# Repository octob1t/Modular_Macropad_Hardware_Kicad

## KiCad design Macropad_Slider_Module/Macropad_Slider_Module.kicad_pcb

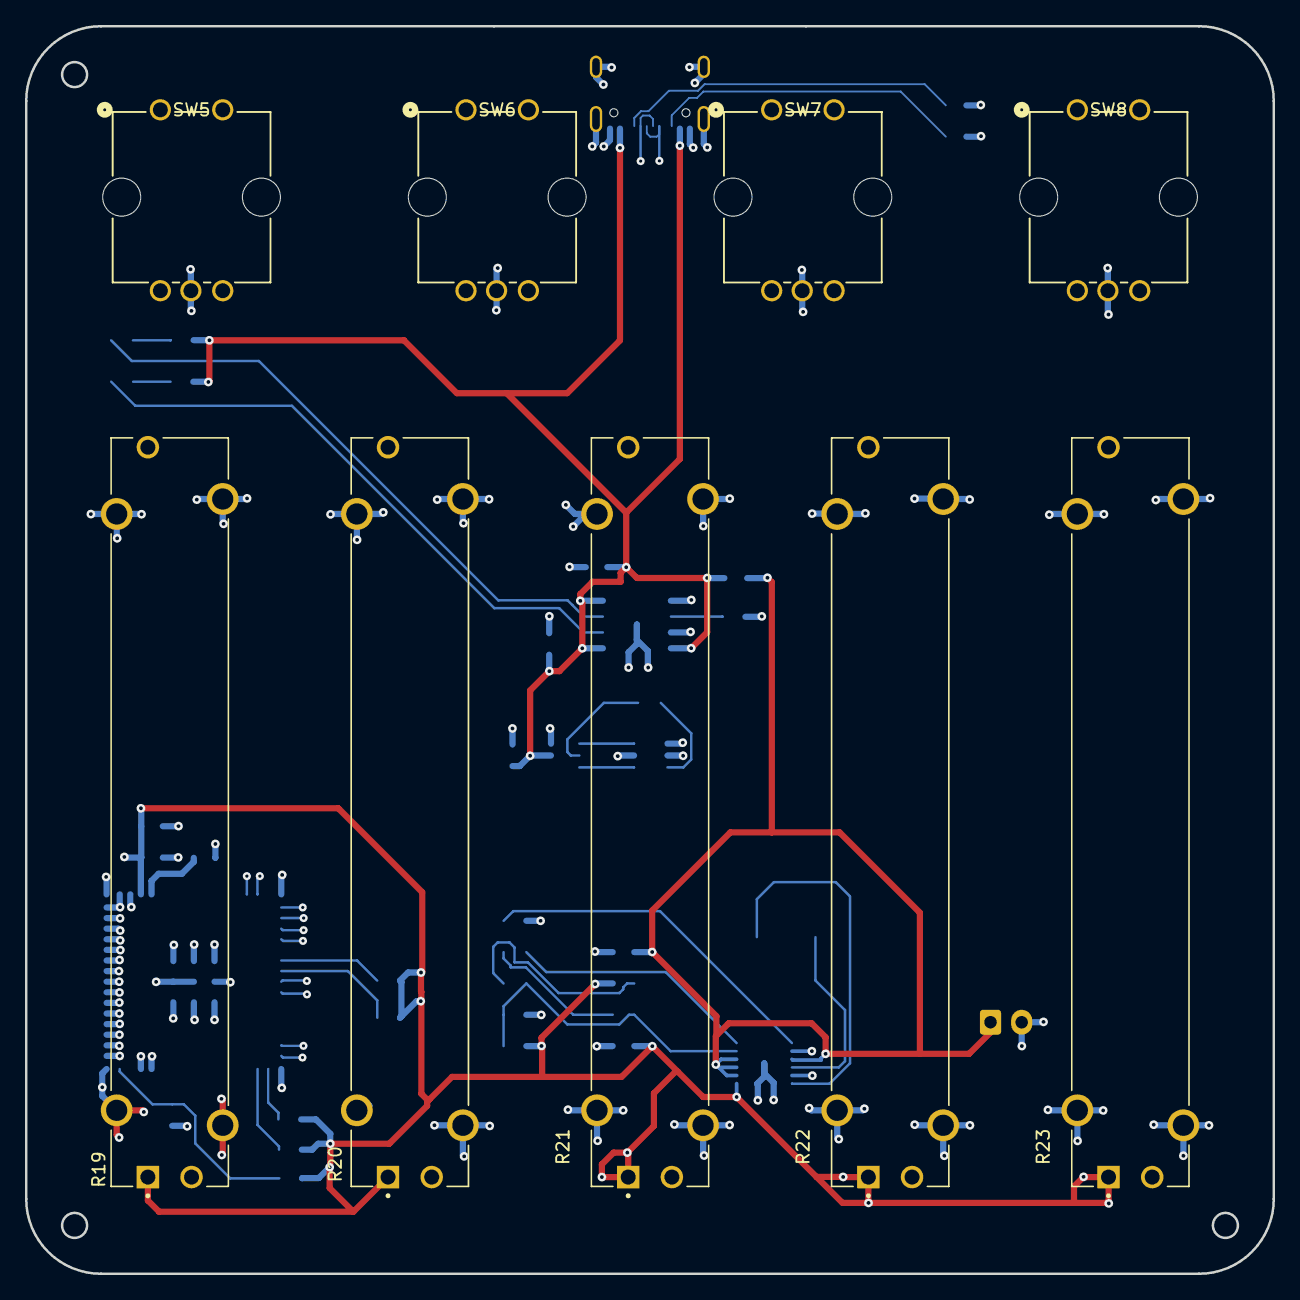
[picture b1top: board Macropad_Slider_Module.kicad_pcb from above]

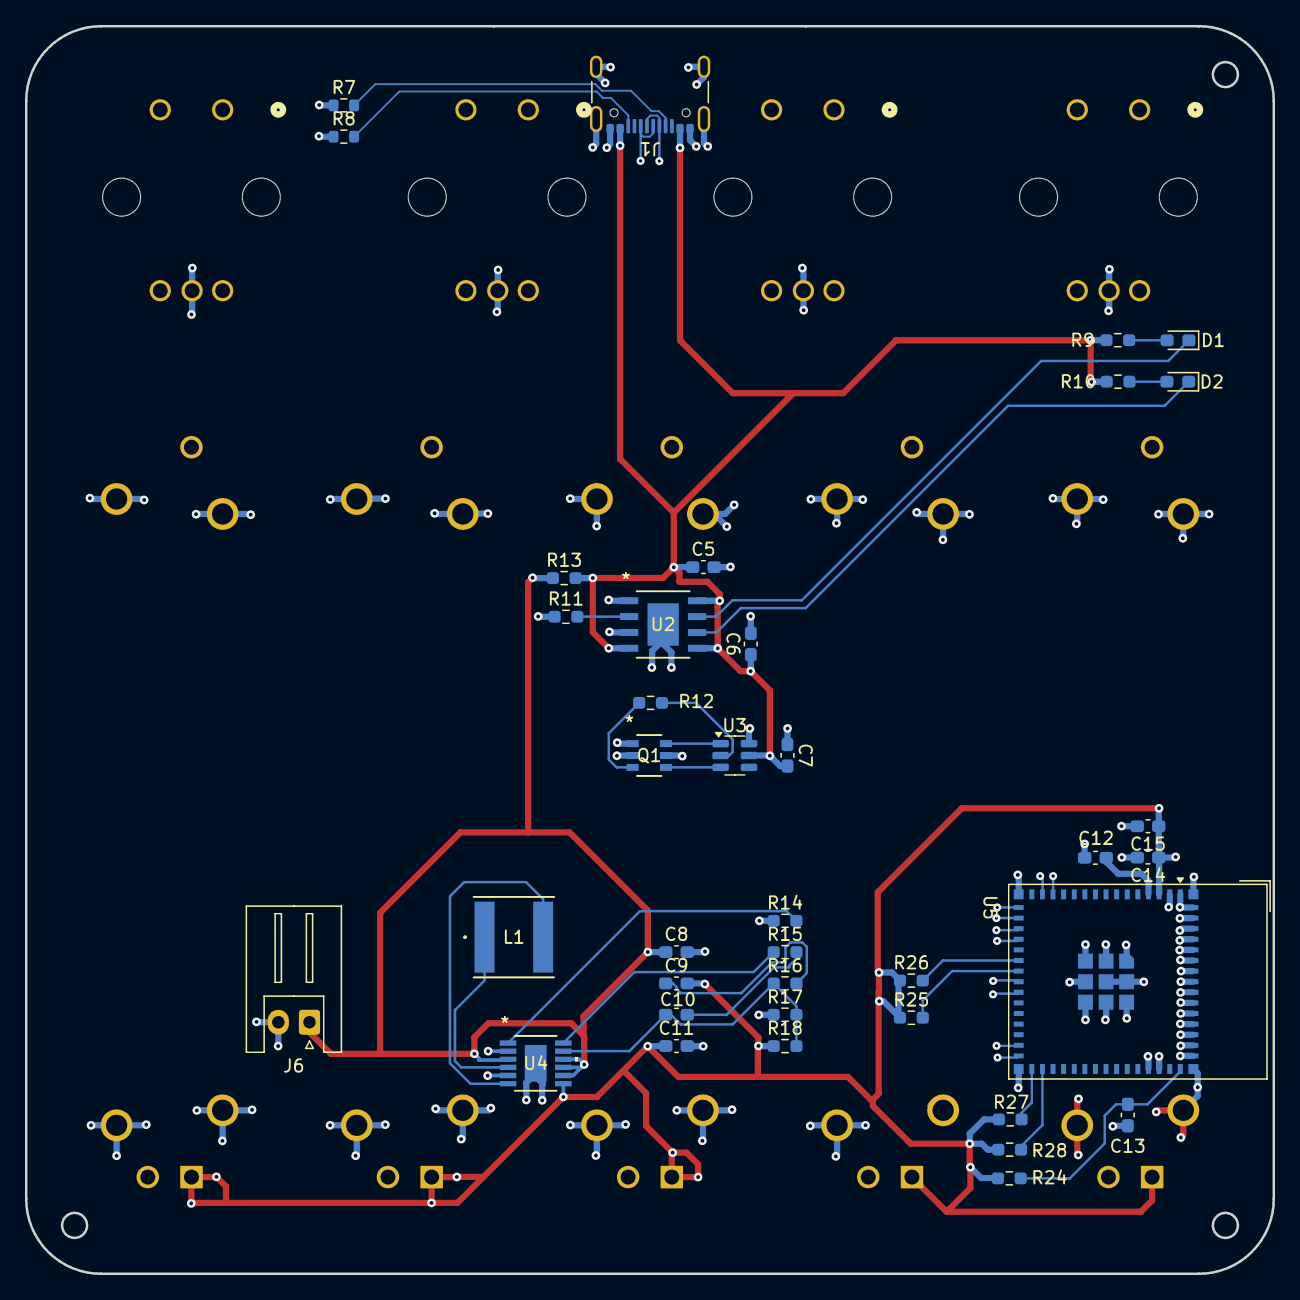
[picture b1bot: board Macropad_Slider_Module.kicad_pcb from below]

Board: 4 copper layers, 100.0 x 100.0 mm, 47 parts (38 on the bottom side), 38 nets.

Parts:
C5, C6, C8, C15: 10uF; C_0603_1608Metric_Pad1.08x0.95mm_HandSolder
C7, C12, C13, C14: .1uF; C_0603_1608Metric_Pad1.08x0.95mm_HandSolder
C9: 47uF; C_0603_1608Metric_Pad1.08x0.95mm_HandSolder
C10: 220pF; C_0603_1608Metric_Pad1.08x0.95mm_HandSolder
C11: 22pF; C_0603_1608Metric_Pad1.08x0.95mm_HandSolder
D1, D2: LED_Small; LED_0603_1608Metric_Pad1.05x0.95mm_HandSolder
J1: USB_C_Receptacle_USB2.0_16P; USB_C_Receptacle_GCT_USB4105-xx-A_16P_TopMnt_Horizontal
J6: Conn_01x02_Socket; JST_XH_S2B-XH-A_1x02_P2.50mm_Horizontal
L1: 4.7uH; IND_TAIYO_NR6028_TAY
Q1: FS8205A; SOT-23-6L_TCP
R7, R8: 5k1; R_0603_1608Metric
R9, R10: 1K; R_0603_1608Metric_Pad0.98x0.95mm_HandSolder
R11: 1K3; R_0603_1608Metric_Pad0.98x0.95mm_HandSolder
R12: 100k; R_0603_1608Metric_Pad0.98x0.95mm_HandSolder
R13: 100; R_0603_1608Metric_Pad0.98x0.95mm_HandSolder
R14: 332k; R_0603_1608Metric_Pad0.98x0.95mm_HandSolder
R15: 49K9; R_0603_1608Metric_Pad0.98x0.95mm_HandSolder
R16: 6K49; R_0603_1608Metric_Pad0.98x0.95mm_HandSolder
R17: 221K; R_0603_1608Metric_Pad0.98x0.95mm_HandSolder
R18: 1000k; R_0603_1608Metric_Pad0.98x0.95mm_HandSolder
R19, R20, R21, R22, R23: PTA4543-2015CPB102; TRIM_PTA4543-2015CPB102
R24: 10K; R_0603_1608Metric_Pad0.98x0.95mm_HandSolder
R25, R26, R27, R28: 10k; R_0603_1608Metric_Pad0.98x0.95mm_HandSolder
SW5, SW6, SW7, SW8: RotaryEncoder; PEC12R-4x15F-Sxxxx_BRN
U2: TP4056; ESOP8_TPW
U3: DW01A; SOT-23-6
U4: LTC3536EMSE-PBF; MSOP-12_MSE_LIT
U5: ESP32-S3-MINI-1; ESP32-S2-MINI-1

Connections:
+3V3: C9.2, C11.1, C14.1, C15.1, R18.1, R19.1, R20.1, R21.1, R22.1, R23.1, R24.1, R25.1, R26.1, R27.1, R28.1, U4.7 (VOUT), U5.3 (3V3)
/BOOT: C12.1, U5.4 (IO0)
/ESP32_EN: C13.1, R24.2, U5.45 (EN)
BAT+: C8.1, J6.1, R13.1, U4.3 (MODE/SYNC), U4.8 (VIN), U4.9 (VIN), U4.10 (*SHDN)
GND: C5.2, C6.2, C7.1, C8.2, C11.2, C12.2, C13.2, C14.2, C15.2, J1.A1 (GND), J1.A12 (GND), J1.B1 (GND), J1.B12 (GND), J1.S1 (SHIELD), J6.2, Q1.1 (S1), Q1.2 (D12), Q1.5 (D12), R7.1, R8.1, R11.1, R14.1, R17.1, R19.SH1 (SHIELD), R19.SH2 (SHIELD__1), R19.SH3 (SHIELD__2), R19.SH4 (SHIELD__3), R20.SH1 (SHIELD), R20.SH2 (SHIELD__1), R20.SH3 (SHIELD__2), R20.SH4 (SHIELD__3), R21.SH1 (SHIELD), R21.SH2 (SHIELD__1), R21.SH3 (SHIELD__2), R21.SH4 (SHIELD__3), R22.SH1 (SHIELD), R22.SH2 (SHIELD__1), R22.SH3 (SHIELD__2), R22.SH4 (SHIELD__3), R23.SH1 (SHIELD), R23.SH2 (SHIELD__1), R23.SH3 (SHIELD__2), R23.SH4 (SHIELD__3), SW5.C, SW6.C, SW7.C, SW8.C, U2.1 (TEMP), U2.3 (GND), U2.9 (GND), U3.6 (GND), U4.2 (SGND), U4.5 (PGND), U4.13 (EPAD), U5.1 (GND), U5.2 (GND), U5.42 (GND), U5.43 (GND), U5.46 (GND), U5.47 (GND), U5.48 (GND), U5.49 (GND), U5.50 (GND), U5.51 (GND), U5.52 (GND), U5.53 (GND), U5.54 (GND), U5.55 (GND), U5.56 (GND), U5.57 (GND), U5.58 (GND), U5.59 (GND), U5.60 (GND), U5.61 (GND), U5.62 (GND), U5.63 (GND), U5.64 (GND), U5.65 (GND)
unnamed: C9.1, R16.2
unnamed: C10.1, R15.2
unnamed: D1.2 (A), R9.2
unnamed: D1.1 (K), U2.7 (*CHRG)
unnamed: D2.2 (A), R10.2
unnamed: D2.1 (K), U2.6 (*STDBY)
unnamed: J1.A5 (CC1), R7.2
unnamed: J1.B5 (CC2), R8.2
unnamed: Q1.6 (G1), U3.1 (OD)
unnamed: Q1.4 (G2), U3.3 (OC)
unnamed: Q1.3 (S2), R12.2
unnamed: R11.2, U2.2 (PROG)
unnamed: R12.1, U3.2 (CS)
unnamed: C10.2, R16.1, R17.2, R18.2, U4.11 (FB)
unnamed: R14.2, U4.1 (RT)
unnamed: L1.1, U4.4 (SW1)
unnamed: L1.2, U4.6 (SW2)
unnamed: R15.1, U4.12 (VC)
unnamed: R26.2, U5.21 (IO17)
unnamed: R25.2, U5.22 (IO18)
unnamed: R27.2, U5.31 (IO35)
unnamed: R28.2, U5.32 (IO36)
R1A: SW5.A, U5.13 (IO9)
R1B: SW5.B, U5.14 (IO10)
R2A: SW6.A, U5.16 (IO12)
R2B: SW6.B, U5.17 (IO13)
R3A: SW7.A, U5.18 (IO14)
R3B: SW7.B, U5.19 (IO15)
R4A: SW8.A, U5.29 (IO34)
R4B: SW8.B, U5.30 (IO48)
USB_N: J1.A7 (D-), J1.B7 (D-), U5.23 (IO19)
USB_P: J1.A6 (D+), J1.B6 (D+), U5.24 (IO20)
VBUS: C5.1, C6.1, C7.2, J1.A4 (VBUS), J1.A9 (VBUS), J1.B4 (VBUS), J1.B9 (VBUS), R9.1, R10.1, R13.2, U2.4 (VCC), U2.5 (BAT), U2.8 (CE), U3.5 (VCC)

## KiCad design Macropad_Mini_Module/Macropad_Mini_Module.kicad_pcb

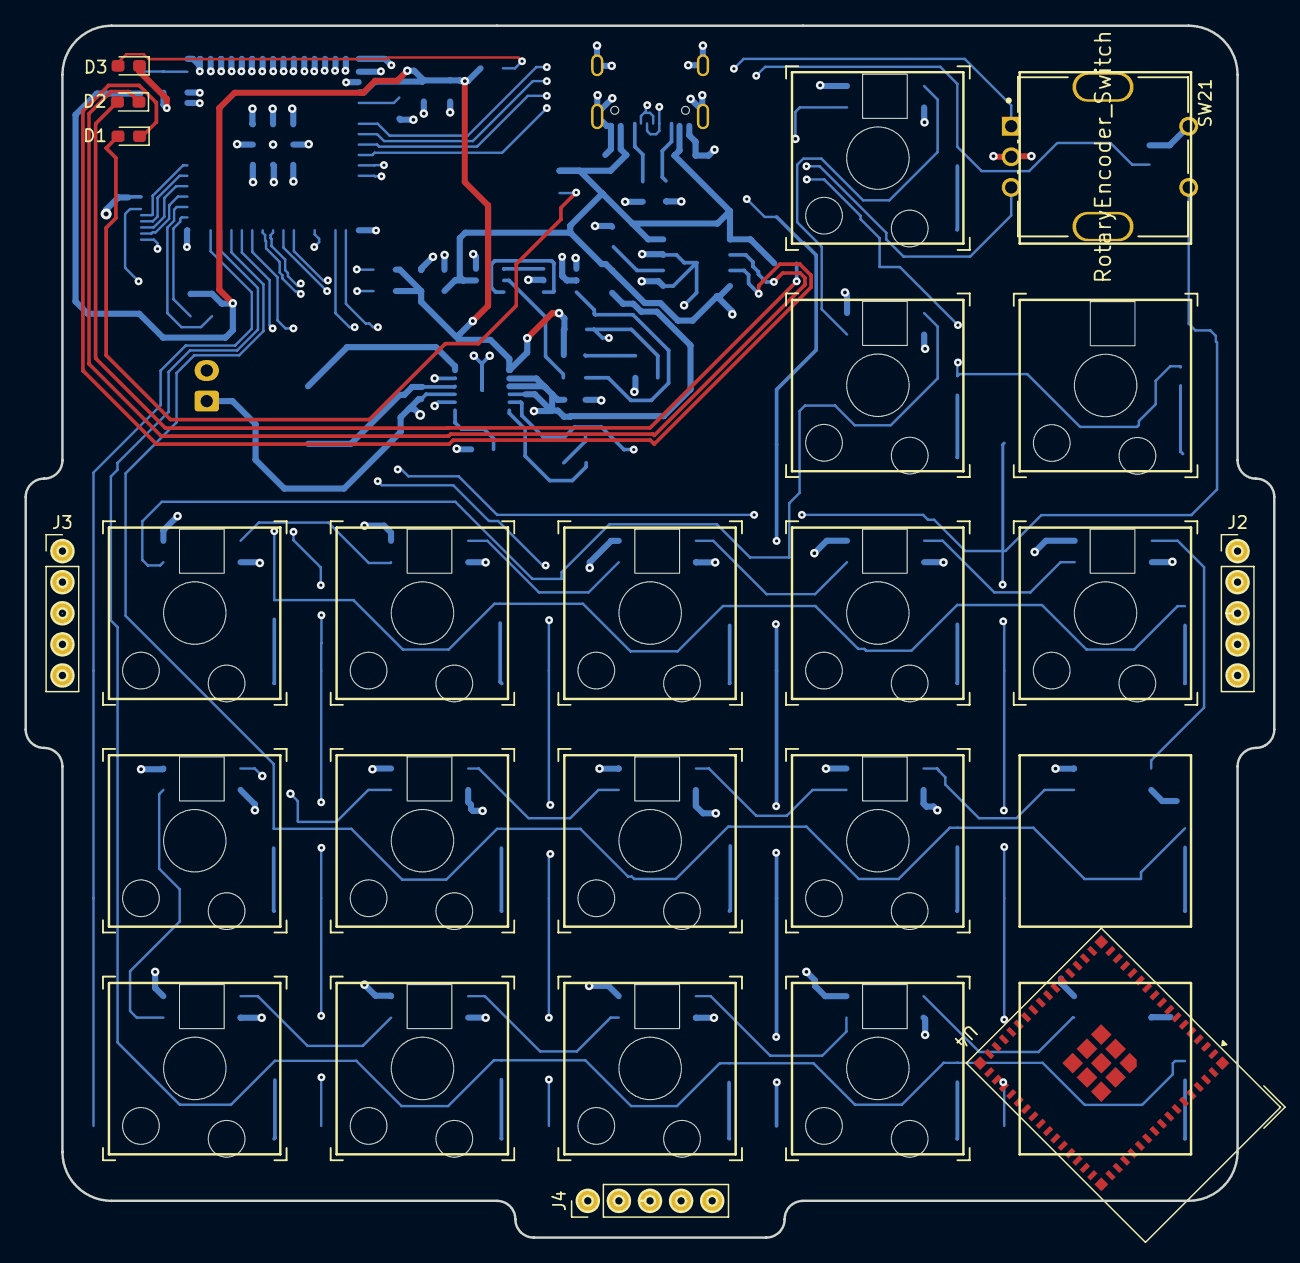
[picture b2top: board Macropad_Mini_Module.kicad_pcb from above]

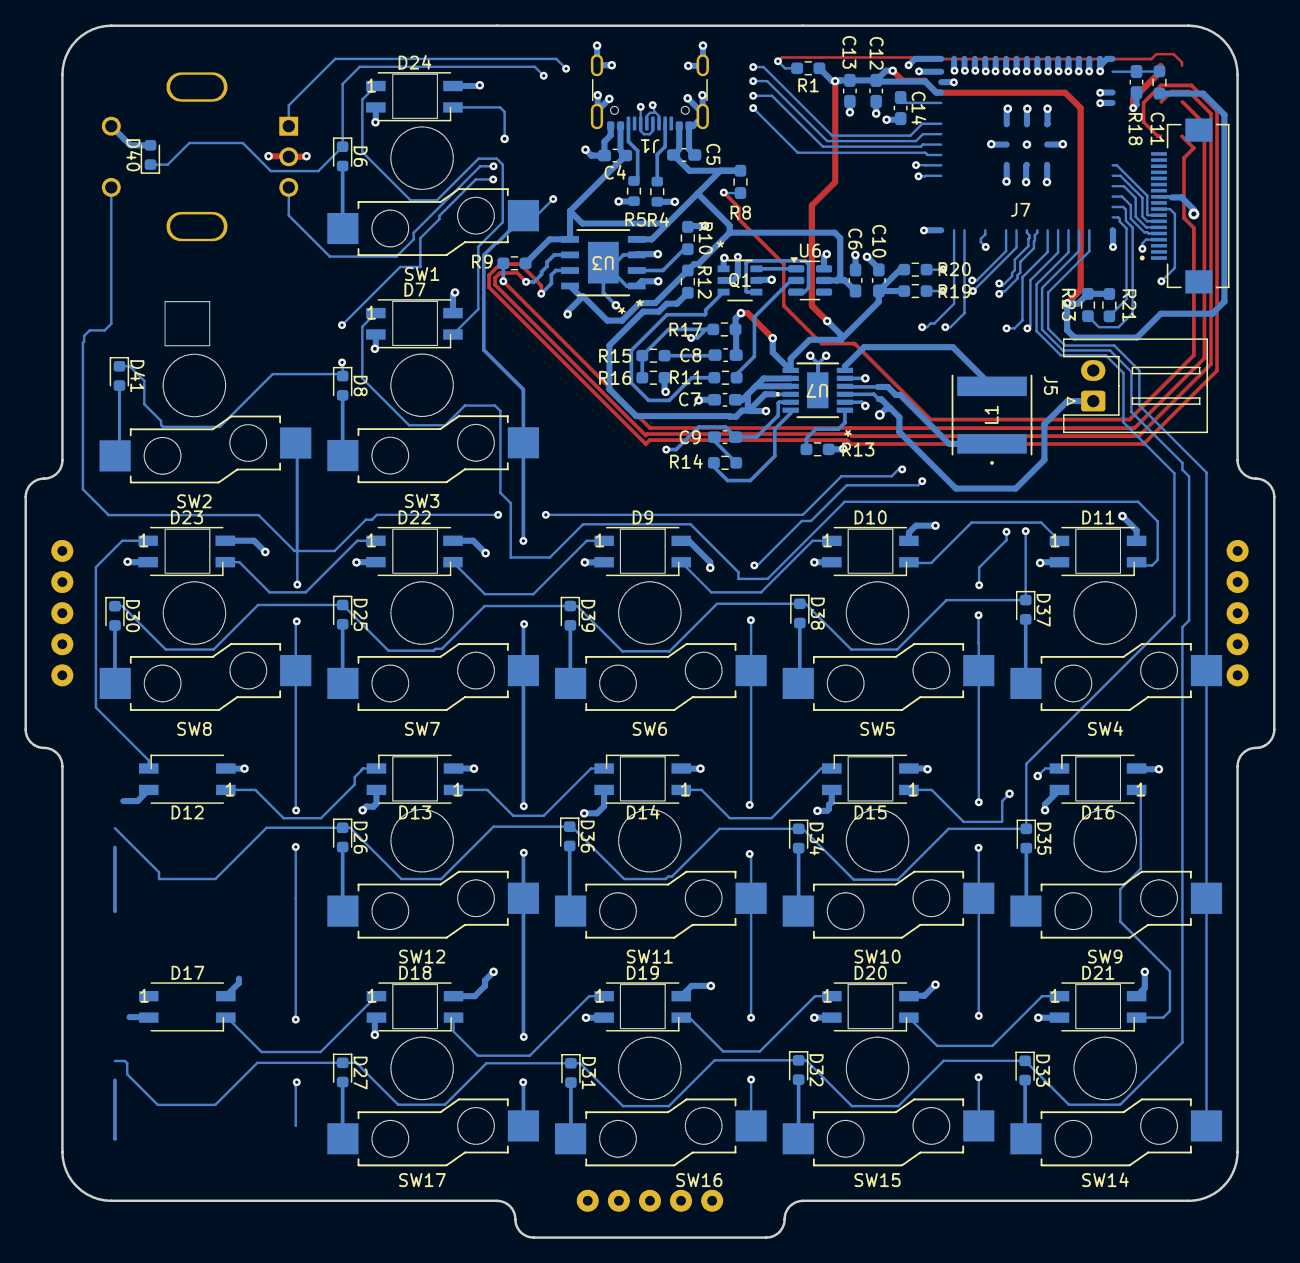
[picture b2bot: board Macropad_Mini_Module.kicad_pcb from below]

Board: 4 copper layers, 102.0 x 99.0 mm, 95 parts (71 on the bottom side), 82 nets.

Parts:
C4, C5, C7, C13: 10uF; C_0603_1608Metric_Pad1.08x0.95mm_HandSolder
C6, C11, C12, C14: .1uF; C_0603_1608Metric_Pad1.08x0.95mm_HandSolder
C8: 47uF; C_0603_1608Metric_Pad1.08x0.95mm_HandSolder
C9: 220pF; C_0603_1608Metric_Pad1.08x0.95mm_HandSolder
C10: 22pF; C_0603_1608Metric_Pad1.08x0.95mm_HandSolder
D1, D2, D3: LED_Small; LED_0603_1608Metric_Pad1.05x0.95mm_HandSolder
D6, D8, D25, D26, D27, D30, D31, D32, D33, D34, D35, D36, D37, D38, D39, D40, D41: D; D_0603_1608Metric
D7, D9, D10, D11, D12, D13, D14, D15, D16, D17, D18, D19, D20, D21, D22, D23, D24: SK6812MINI; LED_SK6812MINI_PLCC4_3.5x3.5mm_P1.75mm_1_Hole_Pads
J1: USB_C_Receptacle_USB2.0_16P; USB_C_Receptacle_GCT_USB4105-xx-A_16P_TopMnt_Horizontal
J2, J3, J4: Conn_01x05_Socket; PinHeader_1x05_P2.54mm_Vertical_Adafruit
J5: Conn_01x02_Socket; JST_XH_S2B-XH-A_1x02_P2.50mm_Horizontal
J7: TF31-18S-0.5SH_800_; HRS_TF31-18S-0.5SH_800_
L1: 4.7uH; IND_TAIYO_NR6028_TAY
Q1: FS8205A; SOT-23-6L_TCP
R1, R8, R9: 1K; R_0603_1608Metric_Pad0.98x0.95mm_HandSolder
R4, R5: 5k1; R_0603_1608Metric
R10: 1K3; R_0603_1608Metric_Pad0.98x0.95mm_HandSolder
R11: 100k; R_0603_1608Metric_Pad0.98x0.95mm_HandSolder
R12: 100; R_0603_1608Metric_Pad0.98x0.95mm_HandSolder
R13: 332k; R_0603_1608Metric_Pad0.98x0.95mm_HandSolder
R14: 49K9; R_0603_1608Metric_Pad0.98x0.95mm_HandSolder
R15: 6K49; R_0603_1608Metric_Pad0.98x0.95mm_HandSolder
R16: 221K; R_0603_1608Metric_Pad0.98x0.95mm_HandSolder
R17: 1000k; R_0603_1608Metric_Pad0.98x0.95mm_HandSolder
R18: 10K; R_0603_1608Metric_Pad0.98x0.95mm_HandSolder
R19, R20, R21, R23: 10k; R_0603_1608Metric_Pad0.98x0.95mm_HandSolder
SW1, SW2, SW3, SW4, SW5, SW6, SW7, SW8, SW9, SW10, SW11, SW12, SW14, SW15, SW16, SW17: SW_MEC_5G; Gateron_Low_Profile_Socket_LED
SW21: RotaryEncoder_Switch; Bourns-PEC11R-4220F-S0024-0-0-0
U3: TP4056; ESOP8_TPW
U4: ESP32-S3-MINI-1; ESP32-S2-MINI-1
U6: DW01A; SOT-23-6
U7: LTC3536EMSE-PBF; MSOP-12_MSE_LIT

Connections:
+3V3: C8.2, C10.1, C12.1, C13.1, R1.1, R17.1, R18.1, R19.1, R20.1, R21.1, R23.1, U4.3 (3V3), U7.7 (VOUT)
/BOOT: C14.1, U4.4 (IO0)
/ESP32_EN: C11.1, R18.2, U4.45 (EN)
/MISO: J7.7, U4.35 (IO39)
/MOSI: J7.6, U4.34 (IO38)
/RST: J7.4, U4.19 (IO15)
/SCK: J7.8, U4.36 (IO40)
/TFTCS: J7.5, U4.33 (IO37)
BAT+: C7.1, J5.1, R12.1, U7.3 (MODE/SYNC), U7.8 (VIN), U7.9 (VIN), U7.10 (*SHDN)
Col0: SW4.1, SW9.1, SW14.1, U4.29 (IO34)
Col1: SW5.1, SW10.1, SW15.1, U4.25 (IO21)
Col2: SW6.1, SW11.1, SW16.1, U4.17 (IO13)
Col3: SW1.1, SW3.1, SW7.1, SW12.1, SW17.1, U4.10 (IO6)
Col4: SW2.1, SW8.1, SW21.S2, U4.16 (IO12)
GND: C4.2, C5.2, C6.1, C7.2, C10.2, C11.2, C12.2, C13.2, C14.2, D3.1 (K), D7.2 (VSS), D9.2 (VSS), D10.2 (VSS), D11.2 (VSS), D12.2 (VSS), D13.2 (VSS), D14.2 (VSS), D15.2 (VSS), D16.2 (VSS), D17.2 (VSS), D18.2 (VSS), D19.2 (VSS), D20.2 (VSS), D21.2 (VSS), D22.2 (VSS), D23.2 (VSS), D24.2 (VSS), J1.A1 (GND), J1.A12 (GND), J1.B1 (GND), J1.B12 (GND), J1.S1 (SHIELD), J5.2, J7.9, Q1.1 (S1), Q1.2 (D12), Q1.5 (D12), R4.1, R5.1, R10.1, R13.1, R16.1, SW21.C, U3.1 (TEMP), U3.3 (GND), U3.9 (GND), U4.1 (GND), U4.2 (GND), U4.42 (GND), U4.43 (GND), U4.46 (GND), U4.47 (GND), U4.48 (GND), U4.49 (GND), U4.50 (GND), U4.51 (GND), U4.52 (GND), U4.53 (GND), U4.54 (GND), U4.55 (GND), U4.56 (GND), U4.57 (GND), U4.58 (GND), U4.59 (GND), U4.60 (GND), U4.61 (GND), U4.62 (GND), U4.63 (GND), U4.64 (GND), U4.65 (GND), U6.6 (GND), U7.2 (SGND), U7.5 (PGND), U7.13 (EPAD)
LED_GPIO: D24.3 (DIN), U4.11 (IO7)
unnamed: C8.1, R15.2
unnamed: C9.1, R14.2
unnamed: D1.2 (A), R8.2
unnamed: D1.1 (K), U3.7 (*CHRG)
unnamed: D2.2 (A), R9.2
unnamed: D2.1 (K), U3.6 (*STDBY)
unnamed: D3.2 (A), R1.2
unnamed: D6.2 (A), SW1.2
unnamed: D8.2 (A), SW3.2
unnamed: D10.3 (DIN), D11.1 (DOUT)
unnamed: D9.3 (DIN), D10.1 (DOUT)
unnamed: D7.1 (DOUT), D11.3 (DIN)
unnamed: D12.3 (DIN), D23.1 (DOUT)
unnamed: D12.1 (DOUT), D13.3 (DIN)
unnamed: D13.1 (DOUT), D14.3 (DIN)
unnamed: D14.1 (DOUT), D15.3 (DIN)
unnamed: D15.1 (DOUT), D16.3 (DIN)
unnamed: D16.1 (DOUT), D21.3 (DIN)
unnamed: D17.3 (DIN), D18.1 (DOUT)
unnamed: D18.3 (DIN), D19.1 (DOUT)
unnamed: D19.3 (DIN), D20.1 (DOUT)
unnamed: D20.3 (DIN), D21.1 (DOUT)
unnamed: D9.1 (DOUT), D22.3 (DIN)
unnamed: D22.1 (DOUT), D23.3 (DIN)
unnamed: D7.3 (DIN), D24.1 (DOUT)
unnamed: D25.2 (A), SW7.2
unnamed: D26.2 (A), SW12.2
unnamed: D27.2 (A), SW17.2
unnamed: D30.2 (A), SW8.2
unnamed: D31.2 (A), SW16.2
unnamed: D32.2 (A), SW15.2
unnamed: D33.2 (A), SW14.2
unnamed: D34.2 (A), SW10.2
unnamed: D35.2 (A), SW9.2
unnamed: D36.2 (A), SW11.2
unnamed: D37.2 (A), SW4.2
unnamed: D38.2 (A), SW5.2
unnamed: D39.2 (A), SW6.2
unnamed: D40.2 (A), SW21.S1
unnamed: D41.2 (A), SW2.2
unnamed: J1.A5 (CC1), R4.2
unnamed: J1.B5 (CC2), R5.2
unnamed: Q1.6 (G1), U6.1 (OD)
unnamed: Q1.4 (G2), U6.3 (OC)
unnamed: Q1.3 (S2), R11.2
unnamed: R10.2, U3.2 (PROG)
unnamed: R20.2, U4.21 (IO17)
unnamed: R19.2, U4.22 (IO18)
unnamed: R21.2, U4.31 (IO35)
unnamed: R23.2, U4.32 (IO36)
unnamed: R11.1, U6.2 (CS)
unnamed: C9.2, R15.1, R16.2, R17.2, U7.11 (FB)
unnamed: R13.2, U7.1 (RT)
unnamed: L1.1, U7.4 (SW1)
unnamed: L1.2, U7.6 (SW2)
unnamed: R14.1, U7.12 (VC)
RotaryA: SW21.A, U4.6 (IO2)
RotaryB: SW21.B, U4.8 (IO4)
Row0: D6.1 (K), D40.1 (K), U4.7 (IO3)
Row1: D8.1 (K), D41.1 (K), U4.9 (IO5)
Row2: D25.1 (K), D30.1 (K), D37.1 (K), D38.1 (K), D39.1 (K), U4.26 (IO26)
Row3: D26.1 (K), D34.1 (K), D35.1 (K), D36.1 (K), U4.27 (IO47)
Row4: D27.1 (K), D31.1 (K), D32.1 (K), D33.1 (K), U4.28 (IO33)
USB_N: J1.A7 (D-), J1.B7 (D-), U4.23 (IO19)
USB_P: J1.A6 (D+), J1.B6 (D+), U4.24 (IO20)
VBUS: C4.1, C5.1, C6.2, D7.4 (VDD), D9.4 (VDD), D10.4 (VDD), D11.4 (VDD), D12.4 (VDD), D13.4 (VDD), D14.4 (VDD), D15.4 (VDD), D16.4 (VDD), D17.4 (VDD), D18.4 (VDD), D19.4 (VDD), D20.4 (VDD), D21.4 (VDD), D22.4 (VDD), D23.4 (VDD), D24.4 (VDD), J1.A4 (VBUS), J1.A9 (VBUS), J1.B4 (VBUS), J1.B9 (VBUS), J7.11, R8.1, R9.1, R12.2, U3.4 (VCC), U3.5 (BAT), U3.8 (CE), U6.5 (VCC)

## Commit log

2025-02-20 Init
2025-02-27 Main_Module v4
    Changed sk6812 properties and footprint. Optimized usb path. Added breakout pads. Added Multiplexer and 5v boost to schematic
